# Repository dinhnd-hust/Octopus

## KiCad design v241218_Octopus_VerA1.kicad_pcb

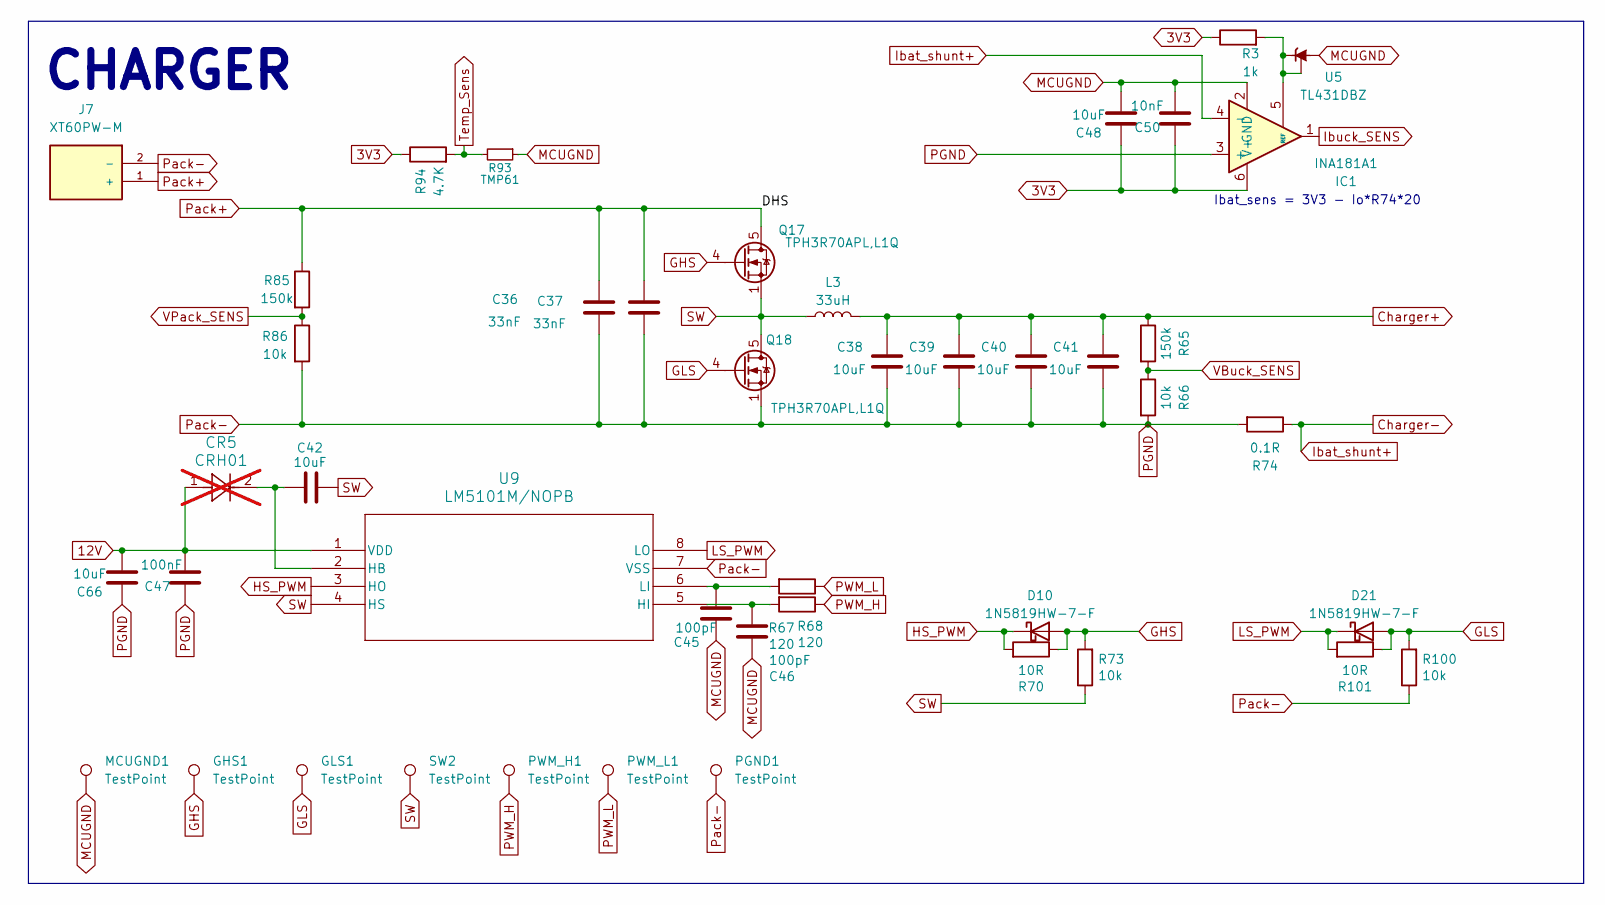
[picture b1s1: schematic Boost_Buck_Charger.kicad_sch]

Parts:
C36, C37: 33nF; C_1206_3216Metric; Mfr. # C1206B104K500NT
C38, C39, C40, C41, C42: 10uF; C_1206_3216Metric; Mfr. # C1206B104K500NT
C45, C46: 100pF; C_0603_1608Metric; Part Number KGQ15ACG1H101JT
C47: 100nF; C_0603_1608Metric; Part Number C0603C104M4RAC
C48, C66: 10uF; C_0603_1608Metric; Mfr. # MCF05KTX160106
C50: 10nF; C_0603_1608Metric; Part Number KAM15AR71H103MT
CR5: CRH01; S-FLAT_TOS; Part Number CRH01(TE85L,Q,M); not fitted
D10, D21: 1N5819HW-7-F; D_SOD-123; Part Number 1N5819HW-7-F
GHS1: TestPoint; TestPoint_Pad_D1.5mm
GLS1: TestPoint; TestPoint_Pad_D1.5mm
IC1: INA181A1; SOT-23-6; Mfr. # INA181A1IDBVR
J7: XT60PW-M; AMASS_XT60PW-M; PARTREV V1.2
L3: 33uH; L_Sunlord_MWSA1204S-2R2; Part Number SRR1280-330M
MCUGND1: TestPoint; TestPoint_Pad_D1.5mm
PGND1: TestPoint; TestPoint_Pad_D1.5mm
PWM_H1: TestPoint; TestPoint_Pad_D1.5mm
PWM_L1: TestPoint; TestPoint_Pad_D1.5mm
Q17, Q18: TPH3R70APL,L1Q; AO_DFN-8-1EP_5.55x5.2mm_P1.27mm_EP4.12x4.6mm; Part Number TPH3R70APL,L1Q
R3: 1k; R_0603_1608Metric; Mfr. # CR0805-FX-1003ELF
R65: 150k; R_0805_2012Metric; Mfr. # CR0805-FX-1003ELF
R66, R86: 10k; R_0805_2012Metric; Mfr. # CR0805-FX-1003ELF
R67, R68: 120; R_0603_1608Metric; Mfr. # CR0603-FX-1002ELF
R70, R101: 10R; R_0603_1608Metric; Part Number RS-05F10R0FT
R73, R100: 10k; R_0603_1608Metric; Part Number RS-03K1002FT
R74: 0.1R; R_2512_6332Metric; Part Number LR122WF100LT4E
R85: 150k; R_0805_2012Metric; Mfr. # CR0805-FX-1503ELF
R93: TMP61; R_0603_1608Metric; Mouser Part Number 595-TMP6131DECR
R94: 4.7K; R_0603_1608Metric; Mfr. # CR0805-FX-1003ELF
SW2: TestPoint; TestPoint_Pad_D1.5mm
U5: TL431DBZ; SOT-23; Part Number TL431BIDBZR
U9: LM5101M/NOPB; M08A; Part Number LM5101AM/NOPB

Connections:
3V3: C48.2, C50.2, IC1.6 (V+), R3.1, R94.1; also elsewhere on the board
12V: C47.1, C66.1, CR5.1, U9.1 (VDD); also elsewhere on the board
Charger+: C38.2, C39.2, C40.2, C41.2, L3.2, R65.1; also elsewhere on the board
Charger-: IC1.4 (-), R74.1; also elsewhere on the board
GHS: D10.2 (A), GHS1.1, Q17.4 (G), R70.1, R73.2
GLS: D21.2 (A), GLS1.1, Q18.4 (G), R100.2, R101.1
HS_PWM: D10.1 (K), R70.2, U9.3 (HO)
Ibuck_SENS: IC1.1; also elsewhere on the board
LS_PWM: D21.1 (K), R101.2, U9.8 (LO)
MCUGND: C45.2, C46.2, C48.1, C50.1, IC1.2 (GND), MCUGND1.1, R93.1, U5.3 (A); also elsewhere on the board
unnamed: IC1.5 (REF), R3.2, U5.1 (K), U5.2 (REF)
unnamed: C42.2, CR5.2, U9.2 (HB)
unnamed: C46.1, R68.2, U9.5 (HI)
unnamed: C45.1, R67.2, U9.6 (LI)
PGND: C36.1, C37.1, C38.1, C39.1, C40.1, C41.1, C47.2, C66.2, IC1.3 (+), J7.2 (-), PGND1.1, Q18.1 (S), Q18.2 (S), Q18.3 (S), R66.2, R74.2, R86.2, R100.1, U9.7 (VSS); also elsewhere on the board
PWM_H: PWM_H1.1, R68.1; also elsewhere on the board
PWM_L: PWM_L1.1, R67.1; also elsewhere on the board
Pack+: C36.2, C37.2, J7.1 (+), Q17.5 (D), R85.1; also elsewhere on the board
SW: C42.1, L3.1, Q17.1 (S), Q17.2 (S), Q17.3 (S), Q18.5 (D), R73.1, SW2.1, U9.4 (HS)
Temp_Sens: R93.2, R94.2; also elsewhere on the board
VBuck_SENS: R65.2, R66.1; also elsewhere on the board
VPack_SENS: R85.2, R86.1; also elsewhere on the board

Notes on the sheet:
Ibat_sens = 3V3 - Io*R74*20
CHARGER

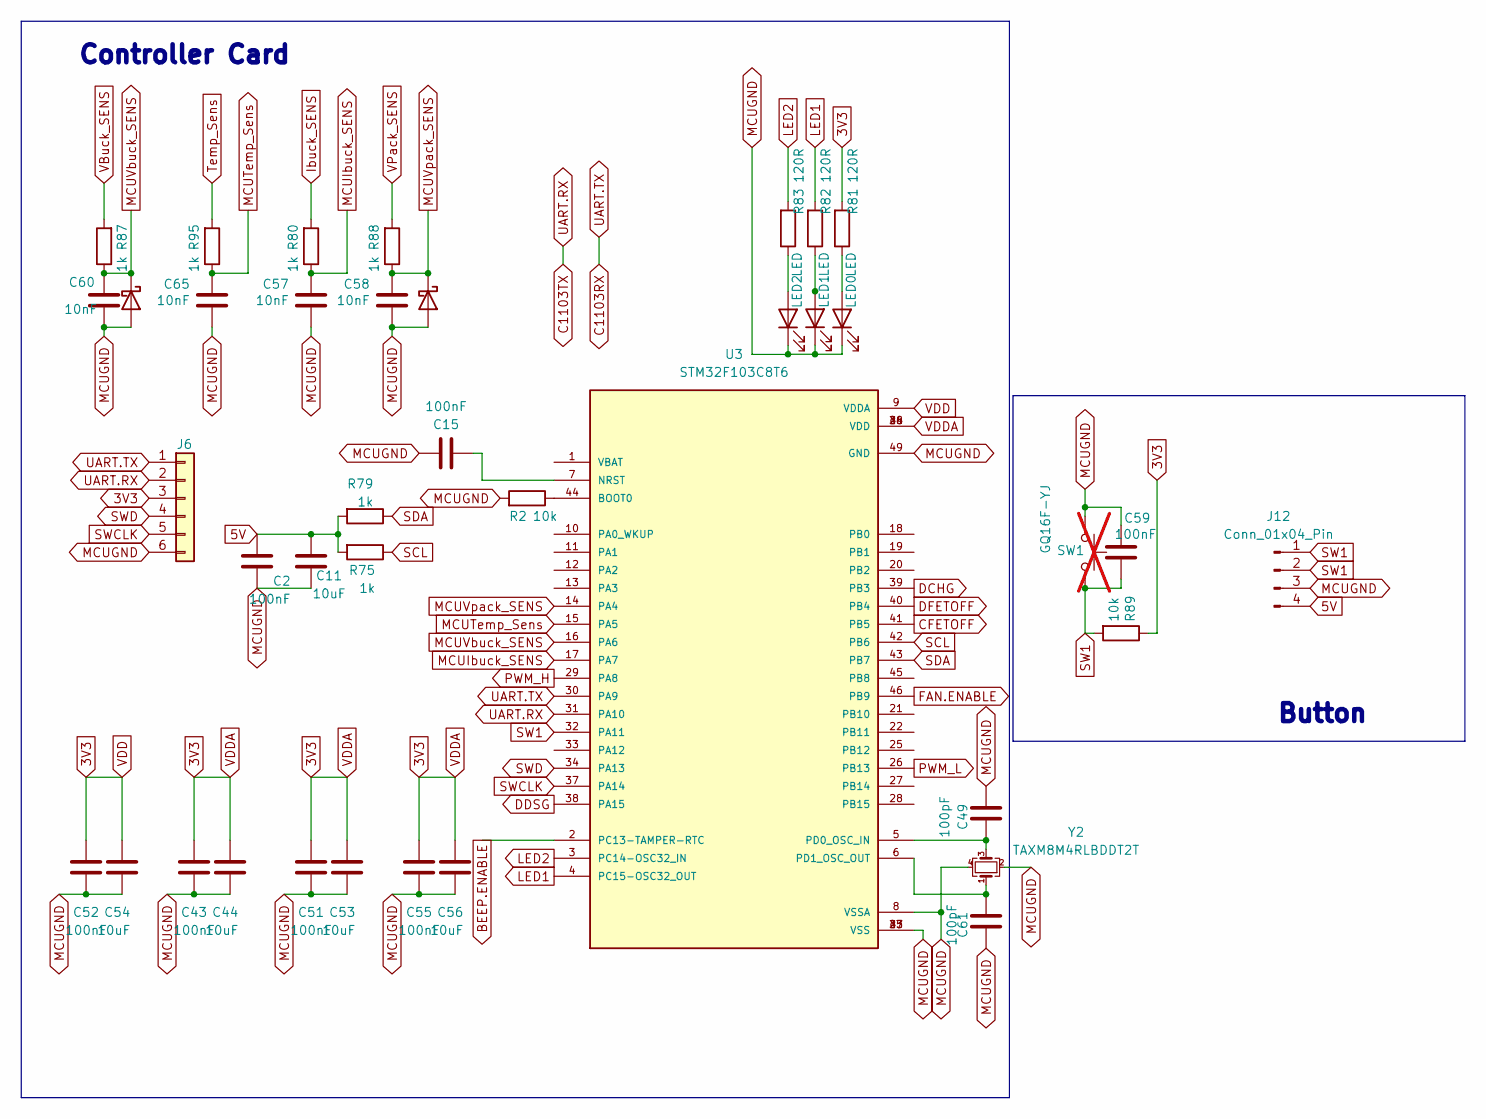
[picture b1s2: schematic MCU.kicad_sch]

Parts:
C2: 100nF; C_0603_1608Metric; Mfr. # MCF05KTX160106
C11: 10uF; C_0603_1608Metric; Mfr. # C2012B104K500NT
C15, C43, C51, C52, C55, C59: 100nF; C_0603_1608Metric; Mfr. # C2012B104K500NT
C44, C53, C54, C56: 10uF; C_0603_1608Metric; Mfr. # MCF05KTX160106
C49, C61: 100pF; C_0603_1608Metric; Mfr. # C2012B104K500NT
C57, C58, C65: 10nF; C_0603_1608Metric; Mfr. # C2012N102J100NT
C60: 10nF; C_0603_1608Metric; Mfr. # C2012N103J100NT
D3, D7: 1N4148; D_SOD-123; Mfr. # 1N4148W
J6: Conn_01x06; Molex_KK-254_AE-6410-06A_1x06_P2.54mm_Vertical; Part Number 22272061
J12: Conn_01x04_Pin; Molex_KK-254_AE-6410-04A_1x04_P2.54mm_Vertical; Part Number 22272041
LED0: LED; LED_0603_1608Metric; Mfr. # Red LED
LED1, LED2: LED; LED_0603_1608Metric; Mfr. # Green LED
R2: 10k; R_0603_1608Metric; Mfr. # CR0805-FX-1001ELF
R75, R79: 1k; R_0603_1608Metric; Mfr. # CR0603-FX-1002ELF
R80, R87, R88, R95: 1k; R_0603_1608Metric; Mfr. # CR0805-FX-1001ELF
R81, R82, R83: 120R; R_0603_1608Metric; Mfr. # CR0805-FX-120R0ELF
R89: 10k; R_0603_1608Metric; Mfr. # CR0603-FX-1002ELF
SW1: GQ16F-YJ; SW_PUSH_6mm; Part Number GQ16F-YJ; not fitted
U3: STM32F103C8T6; LQFP-48-1EP_7x7mm_P0.5mm_EP3.6x3.6mm_ThermalVias; PARTREV 10
Y2: TAXM8M4RLBDDT2T; Crystal_SMD_3225-4Pin_3.2x2.5mm; Part Number TAXM8M4RLBDDT2T

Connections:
3V3: C43.2, C44.1, C51.2, C52.2, C53.1, C54.1, C55.2, C56.1, J6.3, R81.2, R89.1, U3.9 (VDDA), U3.24 (VDD), U3.36 (VDD), U3.48 (VDD); also elsewhere on the board
5V: C2.1, C11.2, J12.4, R75.2, R79.2; also elsewhere on the board
BEEP.ENABLE: U3.2 (PC13-TAMPER-RTC); also elsewhere on the board
C1103RX: J6.1, U3.30 (PA9); also elsewhere on the board
C1103TX: J6.2, U3.31 (PA10); also elsewhere on the board
CFETOFF: U3.41 (PB5); also elsewhere on the board
DCHG: U3.39 (PB3); also elsewhere on the board
DDSG: U3.38 (PA15); also elsewhere on the board
DFETOFF: U3.40 (PB4); also elsewhere on the board
FAN.ENABLE: U3.46 (PB9); also elsewhere on the board
Ibuck_SENS: R80.2; also elsewhere on the board
LED1: R82.2, U3.4 (PC15-OSC32_OUT)
LED2: R83.2, U3.3 (PC14-OSC32_IN)
MCUGND: C2.2, C11.1, C15.1, C43.1, C44.2, C49.2, C51.1, C52.1, C53.2, C54.2, C55.1, C56.2, C57.1, C58.1, C59.2, C60.1, C61.1, C65.1, D3.2 (A), D7.2 (A), J6.6, J12.3, LED0.1 (K), LED1.1 (K), LED2.1 (K), R2.2, SW1.1, U3.8 (VSSA), U3.23 (VSS), U3.35 (VSS), U3.47 (VSS), U3.49 (GND), Y2.2, Y2.4; also elsewhere on the board
MCUIbuck_SENS: C57.2, R80.1, U3.17 (PA7)
MCUTemp_Sens: C65.2, R95.1, U3.15 (PA5)
MCUVbuck_SENS: C60.2, D7.1 (K), R87.1, U3.16 (PA6)
MCUVpack_SENS: C58.2, D3.1 (K), R88.1, U3.14 (PA4)
unnamed: LED0.2 (A), R81.1
unnamed: LED1.2 (A), R82.1
unnamed: LED2.2 (A), R83.1
unnamed: R2.1, U3.44 (BOOT0)
unnamed: C15.2, U3.7 (NRST)
unnamed: C49.1, U3.5 (PD0_OSC_IN), Y2.3
unnamed: C61.2, U3.6 (PD1_OSC_OUT), Y2.1
PWM_H: U3.29 (PA8); also elsewhere on the board
PWM_L: U3.26 (PB13); also elsewhere on the board
SCL: R75.1, U3.42 (PB6); also elsewhere on the board
SDA: R79.1, U3.43 (PB7); also elsewhere on the board
SW1: C59.1, J12.1, J12.2, R89.2, SW1.2, U3.32 (PA11)
SWCLK: J6.5, U3.37 (PA14)
SWD: J6.4, U3.34 (PA13)
Temp_Sens: R95.2; also elsewhere on the board
VBuck_SENS: R87.2; also elsewhere on the board
VPack_SENS: R88.2; also elsewhere on the board

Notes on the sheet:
Button
Controller Card

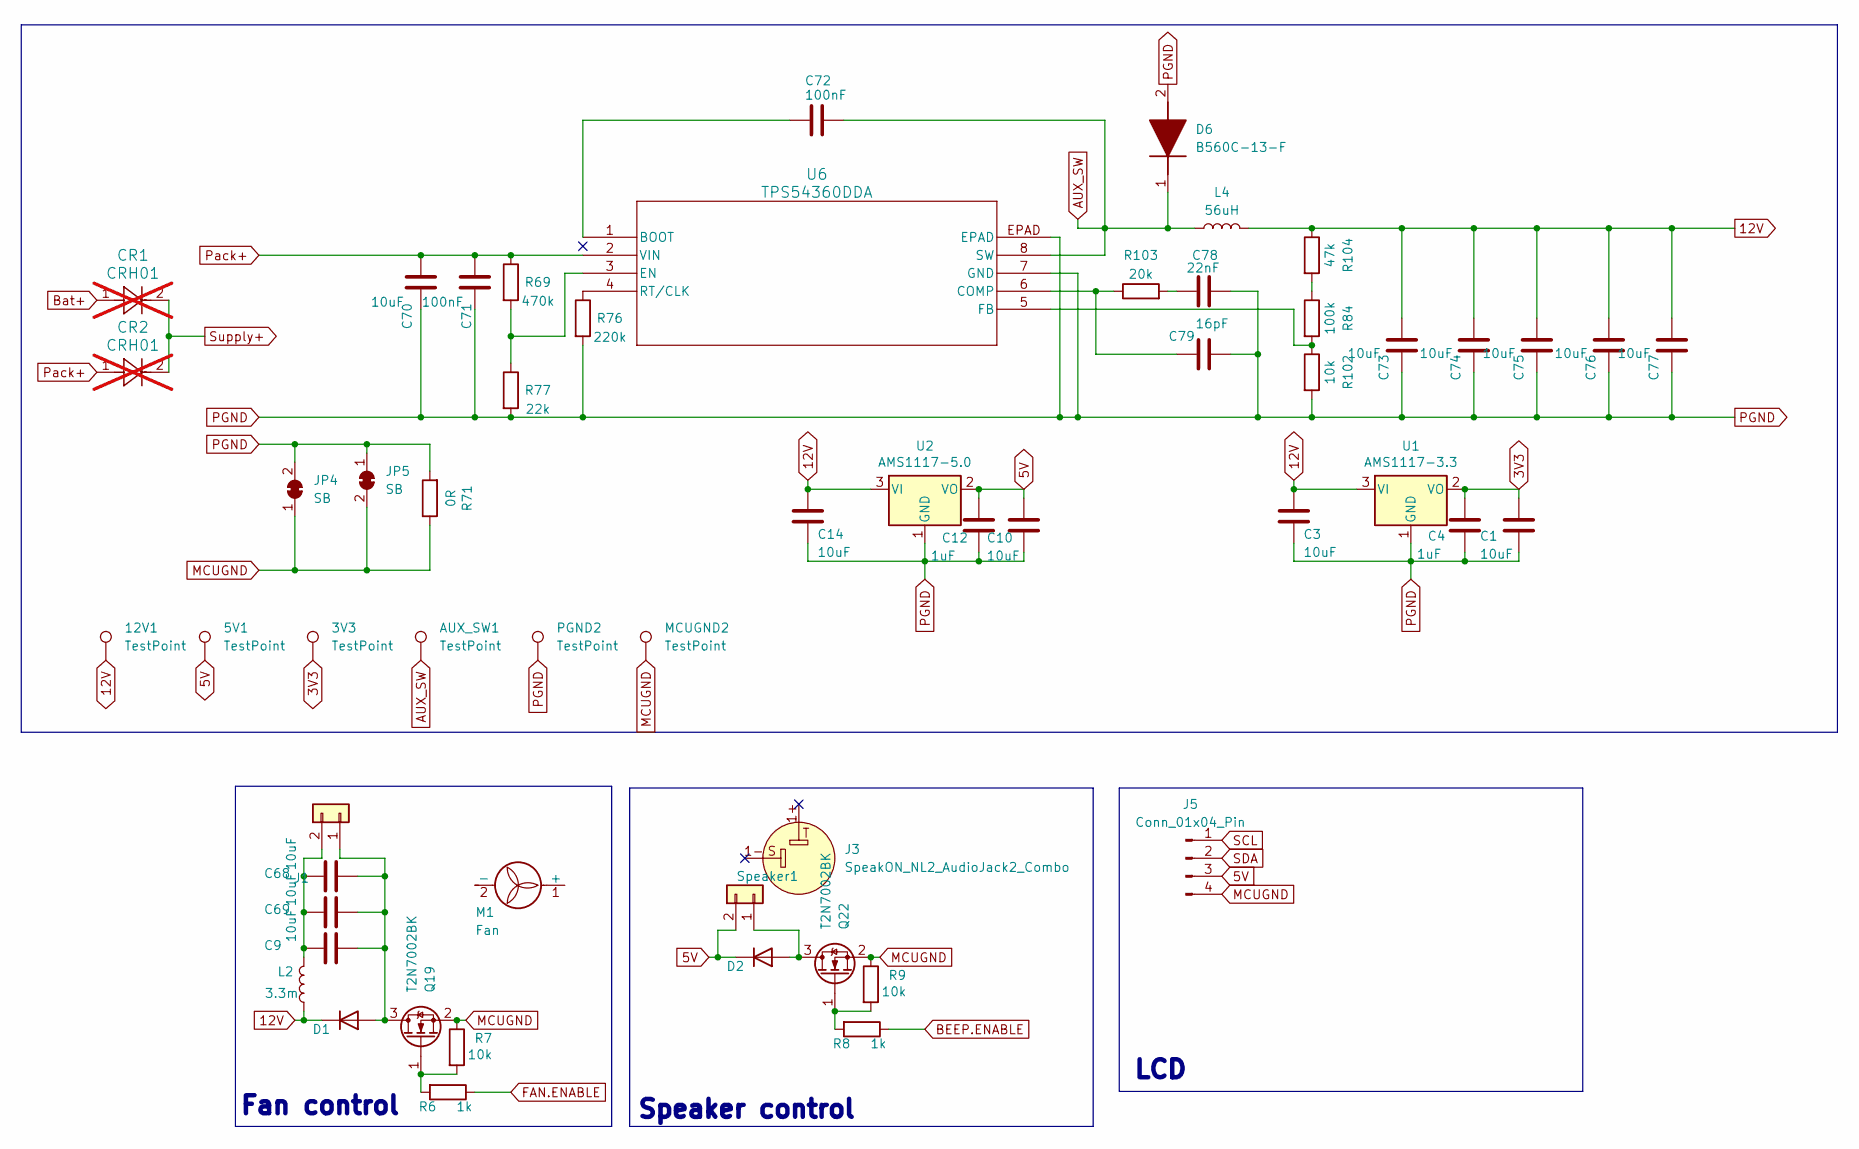
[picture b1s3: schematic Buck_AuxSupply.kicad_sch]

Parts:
3V3, 5V1, 12V1: TestPoint; TestPoint_Pad_D1.5mm
AUX_SW1: TestPoint; TestPoint_Pad_D1.5mm
C1, C3, C10, C14: 10uF; C_0805_2012Metric; Mfr. # MCF05KTX160106
C4, C12: 1uF; C_0805_2012Metric; Mfr. # C2012B104K500NT
C9, C68, C69, C70, C73, C74, C75, C76, C77: 10uF; C_0805_2012Metric; Mfr. # C2012B104K500NT
C71, C72: 100nF; C_0805_2012Metric; Mfr. # C2012B104K500NT
C78: 22nF; C_0805_2012Metric; Mfr. # C2012B104K500NT
C79: 16pF; C_0805_2012Metric; Mfr. # C2012B104K500NT
CR1, CR2: CRH01; S-FLAT_TOS; Part Number CRH01(TE85L,Q,M); not fitted
D1, D2: 1N4148; D_SOD-123; Mfr. # 1N4148W
D6: B560C-13-F; DIOM7959X250N; Mouser Part Number 621-B560C-F
J1: Conn_FAN; Molex_KK-254_AE-6410-02A_1x02_P2.54mm_Vertical; Part Number 0022272021
J3: SpeakON_NL2_AudioJack2_Combo; Part Number TMB12A05
J5: Conn_01x04_Pin; Molex_KK-254_AE-6410-04A_1x04_P2.54mm_Vertical; Part Number 22272041
JP4, JP5: SB; SolderJumper-2_P1.3mm_Bridged2Bar_RoundedPad1.0x1.5mm
L2: 3.3m; L_Axial_L9.5mm_D4.0mm_P2.54mm_Vertical_Fastron_SMCC; Part Number AL0510-332K
L4: 56uH; L_Sunlord_MWSA0804S; Part Number SRR1280-560M
M1: Fan; Fan40x40x20; Mfr. # Fan
MCUGND2: TestPoint; TestPoint_Pad_D1.5mm
PGND2: TestPoint; TestPoint_Pad_D1.5mm
Q19, Q22: T2N7002BK; SOT-23; Part Number T2N7002BK
R6, R8: 1k; R_0603_1608Metric; Mfr. # CR0805-FX-1001ELF
R7, R9: 10k; R_0603_1608Metric; Mfr. # CR0805-FX-1002ELF
R69: 470k; R_0805_2012Metric; Mfr. # CR0805-FX-1004ELF
R71: 0R; R_0603_1608Metric; Part Number RC0603FR-100RL
R76: 220k; R_0805_2012Metric; Mfr. # CR0805-FX-1004ELF
R77: 22k; R_0805_2012Metric; Mfr. # CR0805-FX-1004ELF
R84: 100k; R_0805_2012Metric; Mfr. # CR0805-FX-1003ELF
R102: 10k; R_0805_2012Metric; Mfr. # CR0805-FX-1003ELF
R103: 20k; R_0805_2012Metric; Mfr. # CR0805-FX-1004ELF
R104: 47k; R_0805_2012Metric; Mfr. # CR0805-FX-1003ELF
Speaker1: TMB12A05; MagneticBuzzer_ProSignal_ABI-010-RC; Part Number TMB12A05
U1: AMS1117-3.3; SOT-223-3_TabPin2; Mfr. # TLV1117LV33DCYR
U2: AMS1117-5.0; SOT-223-3_TabPin2; Mfr. # AMS1117-5.0
U6: TPS54360DDA; DDA8_3P1X2P4_TEX-L; Part Number TPS54360DDA

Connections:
3V3: 3V3.1, C1.1, C4.2, U1.2 (VO); also elsewhere on the board
5V: 5V1.1, C10.1, C12.2, D2.1 (K), J5.3, Speaker1.2, U2.2 (VO); also elsewhere on the board
12V: 12V1.1, C3.1, C14.1, C73.2, C74.2, C75.2, C76.2, C77.2, D1.1 (K), L2.1, L4.2, R104.1, U1.3 (VI), U2.3 (VI); also elsewhere on the board
AUX_SW: AUX_SW1.1, C72.2, D6.1 (K), L4.1, U6.8 (SW)
BEEP.ENABLE: R8.1; also elsewhere on the board
FAN.ENABLE: R6.1; also elsewhere on the board
MCUGND: J5.4, JP4.1 (A), JP5.2 (B), MCUGND2.1, Q19.2 (S), Q22.2 (S), R7.1, R9.1, R71.1; also elsewhere on the board
unnamed: C78.1, R103.2
unnamed: CR1.2, CR2.2
unnamed: C9.2, C68.2, C69.2, D1.2 (A), J1.1, Q19.3 (D)
unnamed: D2.2 (A), Q22.3 (D), Speaker1.1
unnamed: C9.1, C68.1, C69.1, J1.2, L2.2
unnamed: Q19.1 (G), R6.2, R7.2
unnamed: Q22.1 (G), R8.2, R9.2
unnamed: R84.1, R104.2
unnamed: C72.1, U6.1 (BOOT)
unnamed: C79.1, R103.1, U6.6 (COMP)
unnamed: R69.2, R77.1, U6.3 (EN)
unnamed: R84.2, R102.1, U6.5 (FB)
unnamed: R76.1, U6.4 (RT/CLK)
PGND: C1.2, C3.2, C4.1, C10.2, C12.1, C14.2, C70.1, C71.1, C73.1, C74.1, C75.1, C76.1, C77.1, C78.2, C79.2, D6.2 (A), JP4.2 (B), JP5.1 (A), PGND2.1, R71.2, R76.2, R77.2, R102.2, U1.1 (GND), U2.1 (GND), U6.7 (GND), U6.EPAD; also elsewhere on the board
Pack+: C70.2, C71.2, CR2.1, R69.1, U6.2 (VIN); also elsewhere on the board
SCL: J5.1; also elsewhere on the board
SDA: J5.2; also elsewhere on the board

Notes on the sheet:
Fan control
Speaker control
LCD

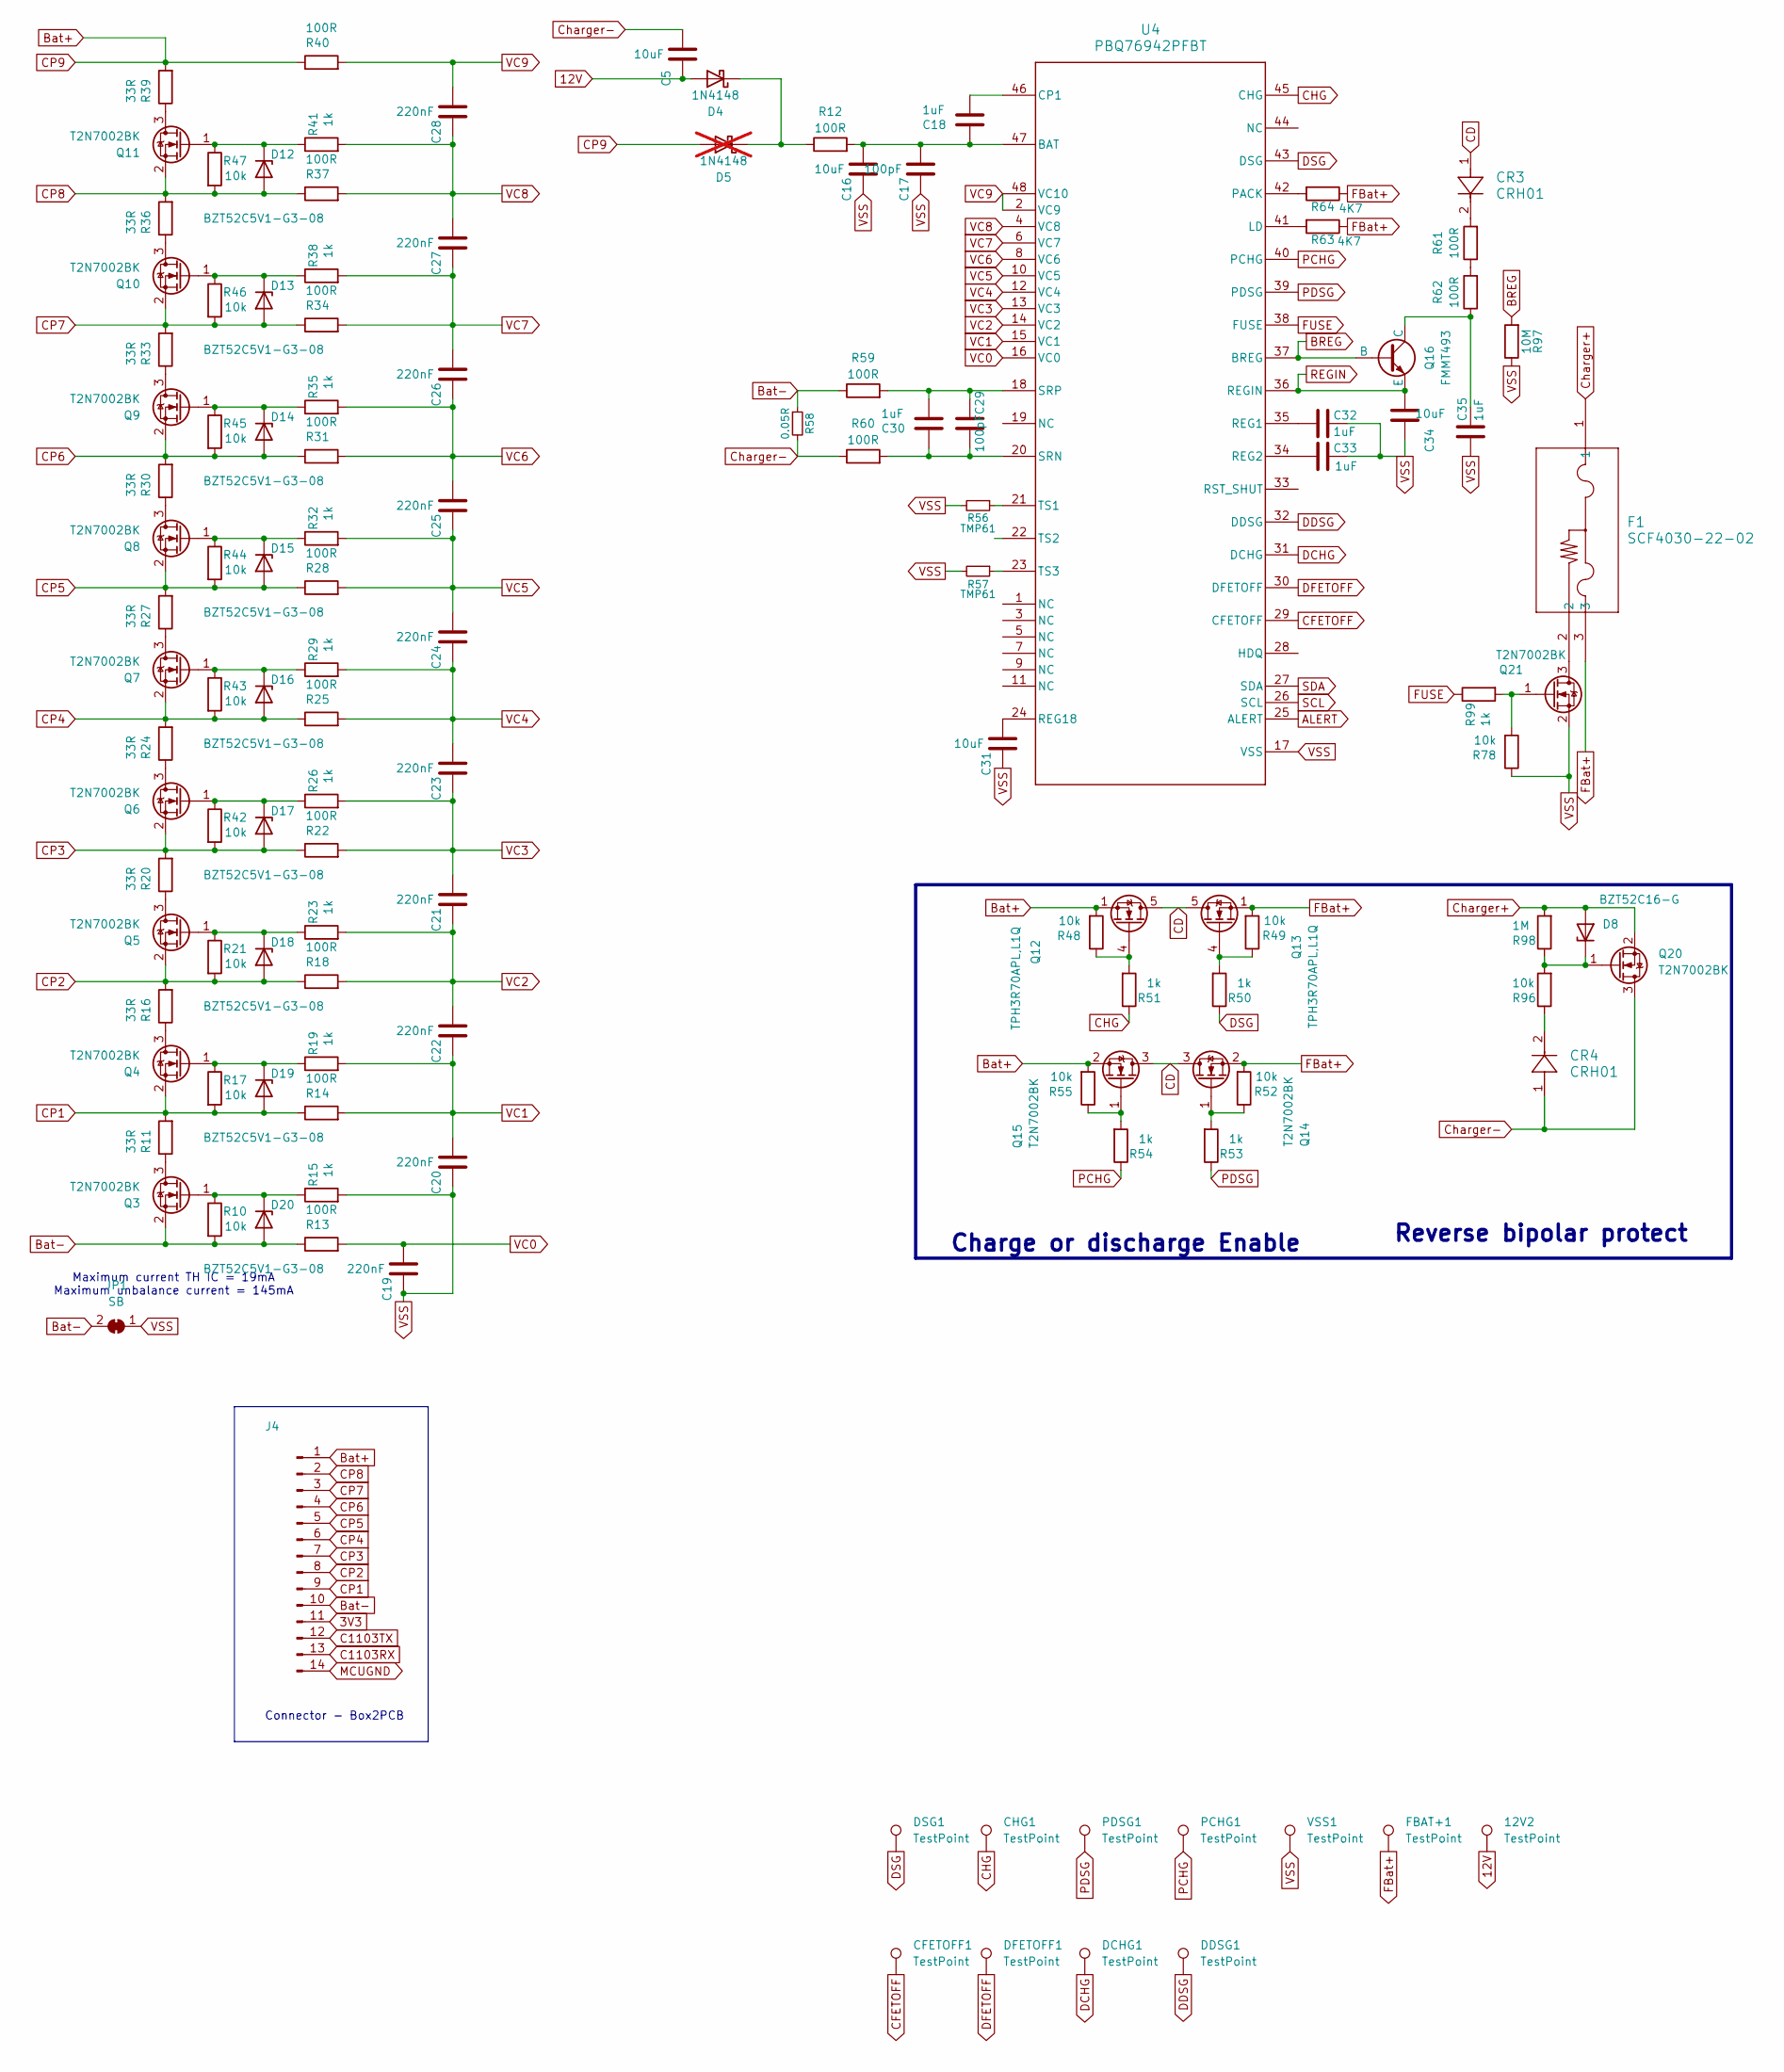
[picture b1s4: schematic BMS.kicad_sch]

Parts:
12V2: TestPoint; TestPoint_Pad_D1.5mm
C5, C16, C34: 10uF; C_0805_2012Metric; Mfr. # C2012B104K500NT
C17, C29: 100pF; C_0603_1608Metric; Mfr. # C2012B104K500NT
C18, C30, C32, C33, C35: 1uF; C_0603_1608Metric; Mfr. # C2012B104K500NT
C19, C20, C21, C22, C23, C24, C25, C26, C27, C28: 220nF; C_0603_1608Metric; Mfr. # C2012B104K500NT
C31: 10uF; C_0603_1608Metric; Mfr. # C2012B104K500NT
CFETOFF1: TestPoint; TestPoint_Pad_D1.5mm
CHG1: TestPoint; TestPoint_Pad_D1.5mm
CR3, CR4: CRH01; S-FLAT_TOS; Part Number CRH01(TE85L,Q,M)
D4: 1N4148; D_SOD-123; Mfr. # 1N4148W
D5: 1N4148; D_SOD-123; Mfr. # 1N4148W; not fitted
D8: BZT52C16-G; D_SOD-123; Part Number BZT52C16-G
D12, D13, D14, D15, D16, D17, D18, D19, D20: BZT52C5V1-G3-08; D_SOD-123; Part Number BZT52C5V1-G3-08
DCHG1: TestPoint; TestPoint_Pad_D1.5mm
DDSG1: TestPoint; TestPoint_Pad_D1.5mm
DFETOFF1: TestPoint; TestPoint_Pad_D1.5mm
DSG1: TestPoint; TestPoint_Pad_D1.5mm
F1: SCF4030-22-02; ITV4030L1212NR_LTF; Part Number SCF4030-22-02
FBAT+1: TestPoint; TestPoint_Pad_D1.5mm
J4: Connector_Bat; Molex_KK-254_AE-6410-14A_1x14_P2.54mm_Vertical; Part Number 22272141
JP1: SB; SolderJumper-2_P1.3mm_Bridged2Bar_RoundedPad1.0x1.5mm
PCHG1: TestPoint; TestPoint_Pad_D1.5mm
PDSG1: TestPoint; TestPoint_Pad_D1.5mm
Q3, Q4, Q5, Q6, Q7, Q8, Q9, Q10, Q11, Q14, Q15, Q20, Q21: T2N7002BK; SOT-23; Part Number T2N7002BK
Q12, Q13: TPH3R70APL,L1Q; AO_DFN-8-1EP_5.55x5.2mm_P1.27mm_EP4.12x4.6mm; Part Number TPH3R70APL,L1Q
Q16: FMMT493; SOT-23; Part Number FMMT493TA
R10, R17, R21, R42, R43, R44, R45, R46, R47, R48, R49, R52, R55, R78, R96: 10k; R_0603_1608Metric; Mfr. # CR0603-FX-1002ELF
R11, R16, R20, R24, R27, R30, R33, R36, R39: 33R; R_0805_2012Metric; Mfr. # CR0805-FX-1002ELF
R12, R59, R60, R61, R62: 100R; R_0603_1608Metric; Mfr. # CR0805-FX-1003ELF
R13, R14, R18, R22, R25, R28, R31, R34, R37, R40: 100R; R_0603_1608Metric; Mfr. # CR0805-FX-1002ELF
R15, R19, R23, R26, R29, R32, R35, R38, R41, R50, R51, R53, R54, R99: 1k; R_0603_1608Metric; Mfr. # CR0603-FX-1002ELF
R56, R57: TMP61; R_0603_1608Metric; Mouser Part Number 595-TMP6131DECR
R58: 0.05R; R_1210_3225Metric; Part Number ERJ-L14KF50MU
R63, R64: 4K7; R_0603_1608Metric; Mfr. # CR0603-FX-1003ELF
R97: 10M; R_0603_1608Metric; Mfr. # CR0603-FX-1003ELF
R98: 1M; R_0603_1608Metric; Mfr. # CR0603-FX-1002ELF
U4: PBQ76942PFBT; PFB0048A_L; Part Number BQ76942PFBR
VSS1: TestPoint; TestPoint_Pad_D1.5mm

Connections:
3V3: J4.11; also elsewhere on the board
12V: 12V2.1, C5.1, D4.2 (A); also elsewhere on the board
ALERT: U4.25 (ALERT)
BREG: Q16.2 (B), R97.2, U4.37 (BREG)
Bat+: D5.2 (A), J4.1, Q12.1 (S), Q12.2 (S), Q12.3 (S), Q15.2 (S), R39.2, R40.1, R48.2, R55.2
Bat-: D20.2 (A), J4.10, JP1.2 (B), Q3.2 (S), R10.2, R13.1, R58.1, R59.1
C1103RX: J4.13; also elsewhere on the board
C1103TX: J4.12; also elsewhere on the board
CD: CR3.1, Q12.5 (D), Q13.5 (D), Q14.3 (D), Q15.3 (D)
CFETOFF: CFETOFF1.1, U4.29 (CFETOFF); also elsewhere on the board
CHG: CHG1.1, R51.1, U4.45 (CHG)
CP1: D19.2 (A), J4.9, Q4.2 (S), R11.2, R14.1, R17.2
CP2: D18.2 (A), J4.8, Q5.2 (S), R16.2, R18.1, R21.2
CP3: D17.2 (A), J4.7, Q6.2 (S), R20.2, R22.1, R42.2
CP4: D16.2 (A), J4.6, Q7.2 (S), R24.2, R25.1, R43.2
CP5: D15.2 (A), J4.5, Q8.2 (S), R27.2, R28.1, R44.2
CP6: D14.2 (A), J4.4, Q9.2 (S), R30.2, R31.1, R45.2
CP7: D13.2 (A), J4.3, Q10.2 (S), R33.2, R34.1, R46.2
CP8: D12.2 (A), J4.2, Q11.2 (S), R36.2, R37.1, R47.2
Charger+: D8.2 (A), F1.1, Q20.2 (S), R98.2; also elsewhere on the board
Charger-: C5.2, CR4.1, Q20.3 (D), R58.2, R60.1; also elsewhere on the board
DCHG: DCHG1.1, U4.31 (DCHG); also elsewhere on the board
DDSG: DDSG1.1, U4.32 (DDSG); also elsewhere on the board
DFETOFF: DFETOFF1.1, U4.30 (DFETOFF); also elsewhere on the board
DSG: DSG1.1, R50.1, U4.43 (DSG)
FBat+: F1.3, FBAT+1.1, Q13.1 (S), Q13.2 (S), Q13.3 (S), Q14.2 (S), R49.2, R52.2, R63.1, R64.1
FUSE: R99.1, U4.38 (FUSE)
MCUGND: J4.14; also elsewhere on the board
unnamed: CR3.2, R61.2
unnamed: CR4.2, R96.1
unnamed: D4.1 (K), D5.1 (K), R12.1
unnamed: D8.1 (K), Q20.1 (G), R96.2, R98.1
unnamed: D12.1 (K), Q11.1 (G), R41.1, R47.1
unnamed: D13.1 (K), Q10.1 (G), R38.1, R46.1
unnamed: D14.1 (K), Q9.1 (G), R35.1, R45.1
unnamed: D15.1 (K), Q8.1 (G), R32.1, R44.1
unnamed: D16.1 (K), Q7.1 (G), R29.1, R43.1
unnamed: D17.1 (K), Q6.1 (G), R26.1, R42.1
unnamed: D18.1 (K), Q5.1 (G), R21.1, R23.1
unnamed: D19.1 (K), Q4.1 (G), R17.1, R19.1
unnamed: D20.1 (K), Q3.1 (G), R10.1, R15.1
unnamed: Q3.3 (D), R11.1
unnamed: Q4.3 (D), R16.1
unnamed: Q5.3 (D), R20.1
unnamed: Q6.3 (D), R24.1
unnamed: Q7.3 (D), R27.1
unnamed: Q8.3 (D), R30.1
unnamed: Q9.3 (D), R33.1
unnamed: Q10.3 (D), R36.1
unnamed: Q11.3 (D), R39.1
unnamed: Q12.4 (G), R48.1, R51.2
unnamed: Q13.4 (G), R49.1, R50.2
unnamed: Q14.1 (G), R52.1, R53.2
unnamed: Q15.1 (G), R54.2, R55.1
unnamed: C35.2, Q16.1 (C), R62.1
unnamed: F1.2, Q21.3 (D)
unnamed: Q21.1 (G), R78.2, R99.2
unnamed: R61.1, R62.2
unnamed: C16.2, C17.2, C18.1, R12.2, U4.47 (BAT)
unnamed: C18.2, U4.46 (CP1)
unnamed: R63.2, U4.41 (LD)
unnamed: R64.2, U4.42 (PACK)
unnamed: C32.1, U4.35 (REG1)
unnamed: C33.1, U4.34 (REG2)
unnamed: C31.2, U4.24 (REG18)
unnamed: C29.1, C30.1, R60.2, U4.20 (SRN)
unnamed: C29.2, C30.2, R59.2, U4.18 (SRP)
unnamed: R56.1, U4.21 (TS1)
unnamed: R57.1, U4.23 (TS3)
PCHG: PCHG1.1, R54.1, U4.40 (PCHG)
PDSG: PDSG1.1, R53.1, U4.39 (PDSG)
REGIN: C34.2, Q16.3 (E), U4.36 (REGIN)
SCL: U4.26 (SCL); also elsewhere on the board
SDA: U4.27 (SDA); also elsewhere on the board
VC0: C19.2, R13.2, U4.16 (VC0)
VC1: C20.2, C22.1, R14.2, R19.2, U4.15 (VC1)
VC2: C21.1, C22.2, R18.2, R23.2, U4.14 (VC2)
VC3: C21.2, C23.1, R22.2, R26.2, U4.13 (VC3)
VC4: C23.2, C24.1, R25.2, R29.2, U4.12 (VC4)
VC5: C24.2, C25.1, R28.2, R32.2, U4.10 (VC5)
VC6: C25.2, C26.1, R31.2, R35.2, U4.8 (VC6)
VC7: C26.2, C27.1, R34.2, R38.2, U4.6 (VC7)
VC8: C27.2, C28.1, R37.2, R41.2, U4.4 (VC8)
VC9: C28.2, R40.2, U4.2 (VC9), U4.48 (VC10)
VSS: C16.1, C17.1, C19.1, C20.1, C31.1, C32.2, C33.2, C34.1, C35.1, JP1.1 (A), Q21.2 (S), R15.2, R56.2, R57.2, R78.1, R97.1, U4.17 (VSS), VSS1.1

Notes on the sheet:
Connector - Box2PCB
Reverse bipolar protect
Charge or discharge Enable
Maximum current TH IC = 19mA Maximum unbalance current = 145mA

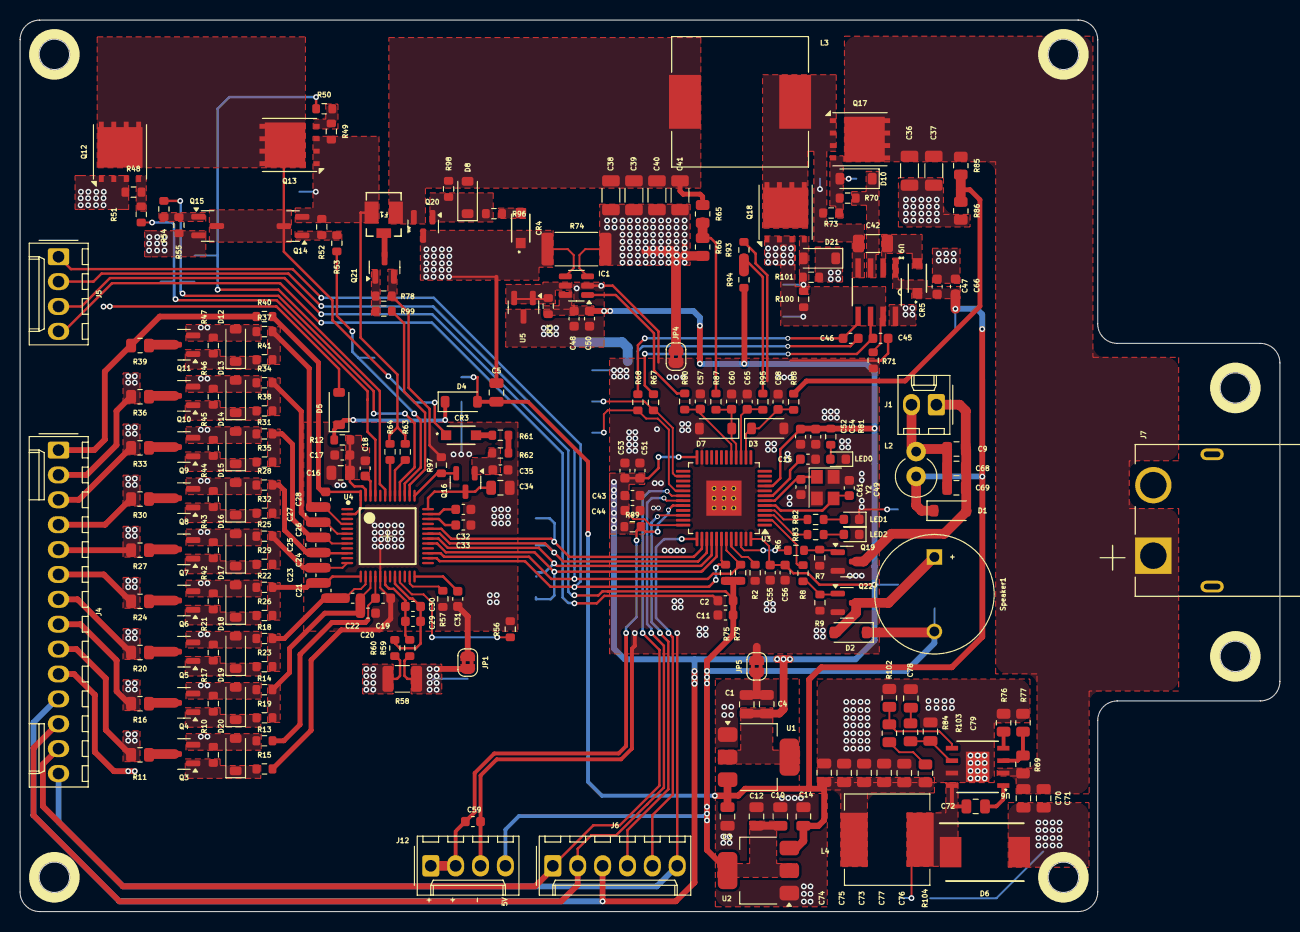
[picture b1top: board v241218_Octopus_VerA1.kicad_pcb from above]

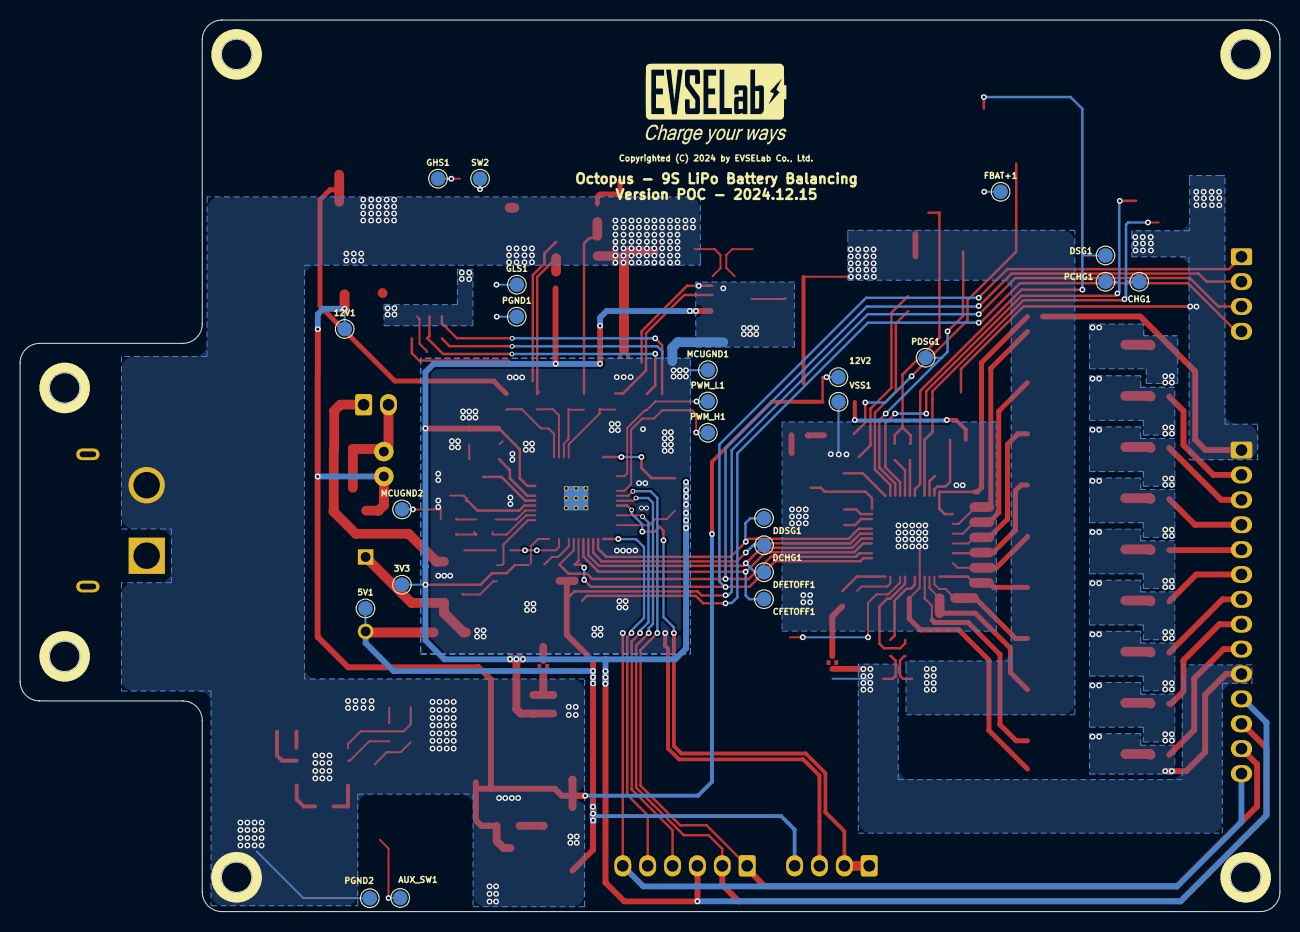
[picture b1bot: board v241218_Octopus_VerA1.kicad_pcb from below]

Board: 2 copper layers, 128.6 x 91.0 mm, 260 parts (24 on the bottom side), 133 nets.

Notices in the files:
v241218_Octopus_VerA1.kicad_pcb:
Copyrighted (C) 2024 by EVSELab Co., Ltd.
